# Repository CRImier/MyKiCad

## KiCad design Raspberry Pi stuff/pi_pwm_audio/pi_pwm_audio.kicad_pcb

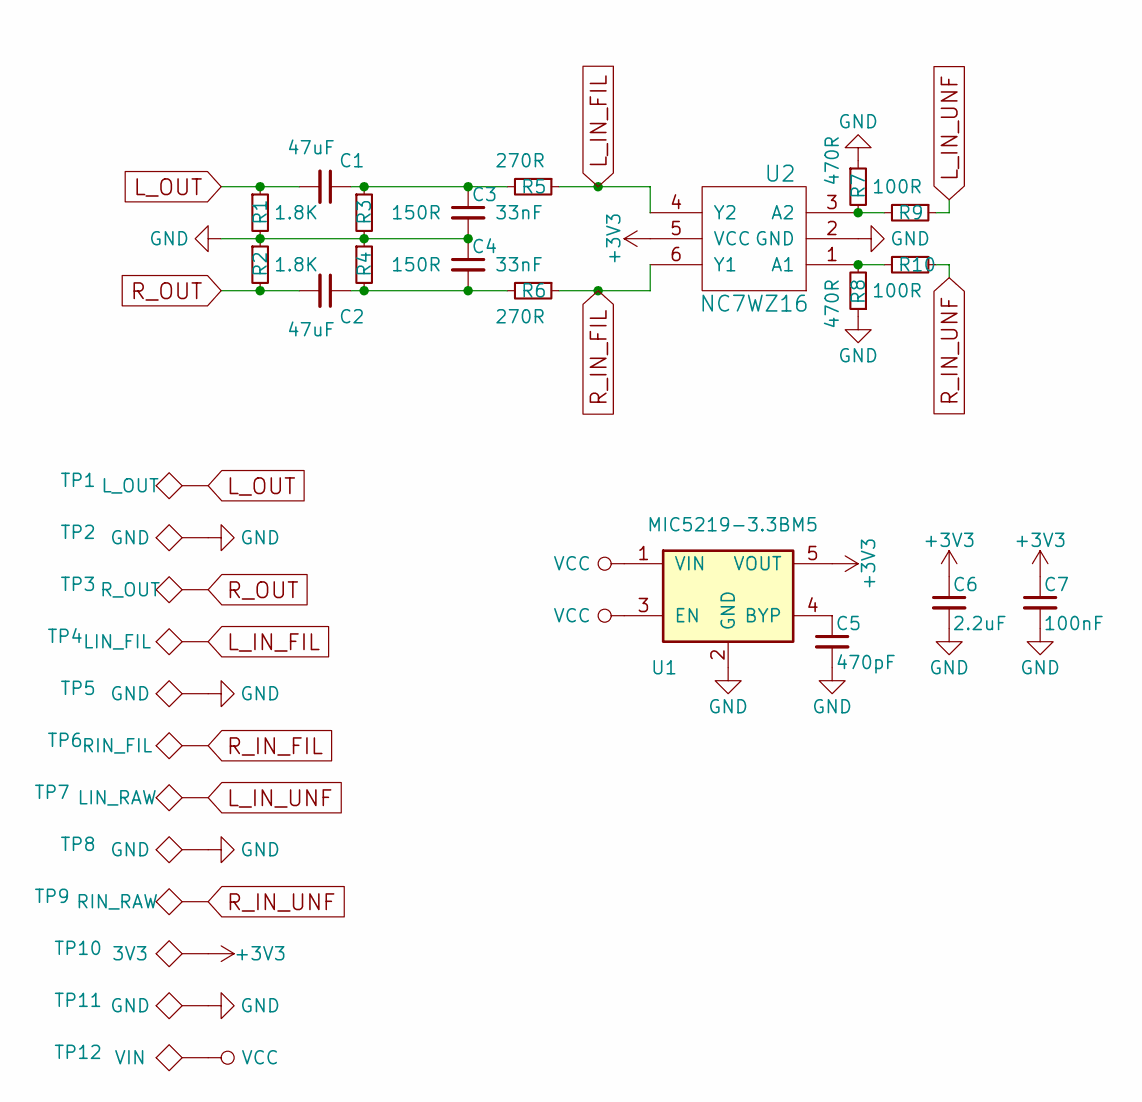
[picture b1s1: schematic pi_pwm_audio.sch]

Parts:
C1, C2: 47uF; C_1206_HandSoldering
C3, C4: 33nF; C_0603_HandSoldering
C5: 470pF; C_0603_HandSoldering
C6: 2.2uF; C_0805_HandSoldering
C7: 100nF; C_0805_HandSoldering
R1, R2: 1.8K; R_0603_HandSoldering
R3, R4: 150R; R_0603_HandSoldering
R5, R6: 270R; R_0603_HandSoldering
R7, R8: 470R; R_0603_HandSoldering
R9, R10: 100R; R_0603_HandSoldering
TP1: L_OUT; Measurement_Point_Round-TH_Small
TP2, TP5, TP8: GND; Measurement_Point_Square-TH_Small
TP3: R_OUT; Measurement_Point_Round-TH_Small
TP4: LIN_FIL; Measurement_Point_Round-TH_Small
TP6: RIN_FIL; Measurement_Point_Round-TH_Small
TP7: LIN_RAW; Measurement_Point_Round-TH_Small
TP9: RIN_RAW; Measurement_Point_Round-TH_Small
TP10: 3V3; Measurement_Point_Round-SMD-Pad_Small
TP11: GND; Measurement_Point_Round-SMD-Pad_Small
TP12: VIN; Measurement_Point_Round-TH_Small
U1: MIC5219-3.3BM5; SOT-23-5
U2: NC7WZ16; SOT-363_SC-70-6_Handsoldering

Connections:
+3V3: C6.1, C7.1, TP10.1, U1.5 (VOUT), U2.5 (VCC)
GND: C3.2, C4.1, C5.2, C6.2, C7.2, R1.2, R2.1, R3.2, R4.1, R7.1, R8.1, TP2.1, TP5.1, TP8.1, TP11.1, U1.2 (GND), U2.2 (GND)
L_IN_FIL: R5.1, TP4.1, U2.4 (Y2)
L_IN_UNF: R9.1, TP7.1
L_OUT: C1.2, R1.1, TP1.1
unnamed: C1.1, C3.1, R3.1, R5.2
unnamed: C2.1, C4.2, R4.2, R6.2
unnamed: C5.1, U1.4 (BYP)
unnamed: R7.2, R9.2, U2.3 (A2)
unnamed: R8.2, R10.2, U2.1 (A1)
R_IN_FIL: R6.1, TP6.1, U2.6 (Y1)
R_IN_UNF: R10.1, TP9.1
R_OUT: C2.2, R2.2, TP3.1
VCC: TP12.1, U1.1 (VIN), U1.3 (EN)

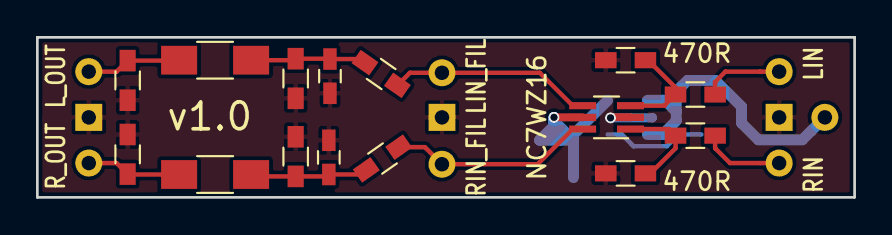
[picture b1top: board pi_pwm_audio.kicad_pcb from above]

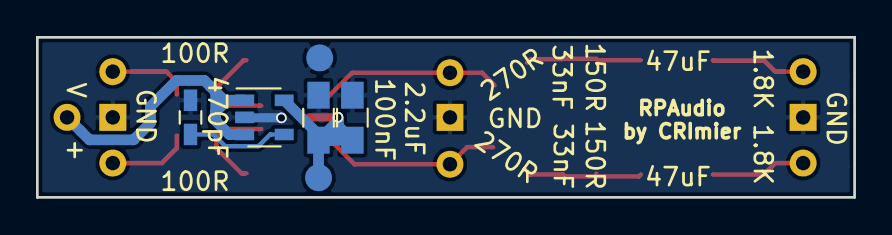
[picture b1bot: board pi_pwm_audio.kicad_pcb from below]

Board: 2 copper layers, 45.4 x 8.9 mm, 31 parts (6 on the bottom side), 14 nets.

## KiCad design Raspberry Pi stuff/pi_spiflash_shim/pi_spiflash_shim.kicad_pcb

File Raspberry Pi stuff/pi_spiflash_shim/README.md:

# Pi SPI flash shim

This board lets you reprogram SPI flash chips easily, by soldering the chip onto this board
and then plugging this board straight onto a Raspberry Pi GPIO header. Then, use something like flashrom.

The SPI chip is hardwired to CS0. The pin header holes are staggered in a way that should ensure
good mechanical contact of the plated holes to the Pi, without need for soldering.

Silkscreen markings on this board shows how many pin pairs you need to leave above and below,
decreasing the risk of you mis-plugging it.

This board is untested and there's no guarantees of fitness.

- Software: Kicad 6
- Version: 1
- PCB size: 19.05x12.7mm
- Layer count: 2
- Recommended thickness: whatever

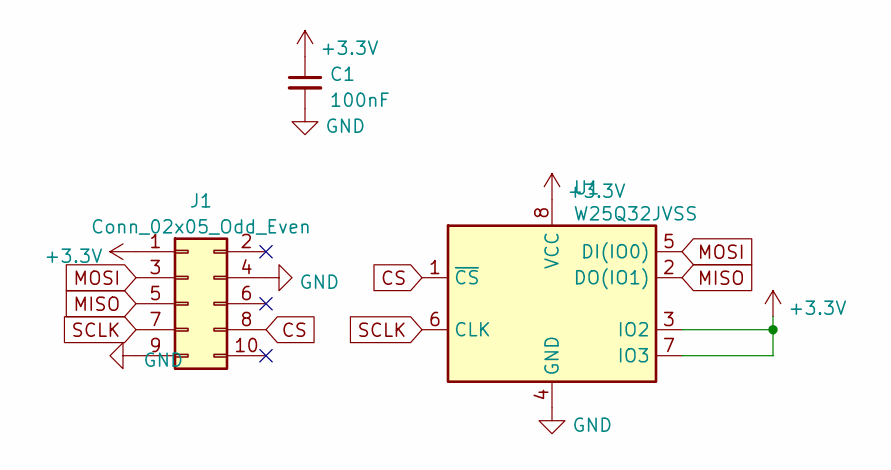
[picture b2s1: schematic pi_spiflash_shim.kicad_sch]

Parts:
C1: 100nF; C_0603_1608Metric
J1: Conn_02x05_Odd_Even; PinHeader_2x05_P2.54mm_Vertical
U1: W25Q32JVSS; SOIC-8_5.23x5.23mm_P1.27mm

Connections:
+3.3V: C1.1, J1.1, U1.3 (IO2), U1.7 (IO3), U1.8 (VCC)
CS: J1.8, U1.1 (~CS)
GND: C1.2, J1.4, J1.9, U1.4 (GND)
MISO: J1.5, U1.2 (DO(IO1))
MOSI: J1.3, U1.5 (DI(IO0))
SCLK: J1.7, U1.6 (CLK)

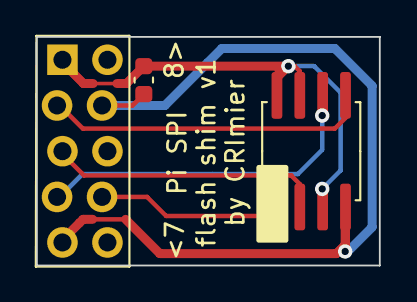
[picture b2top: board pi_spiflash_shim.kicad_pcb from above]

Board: 2 copper layers, 19.0 x 12.7 mm, 3 parts (0 on the bottom side), 6 nets.

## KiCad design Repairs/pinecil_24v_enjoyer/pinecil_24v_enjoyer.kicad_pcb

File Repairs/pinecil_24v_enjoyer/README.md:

# Pinecil 24V enjoyer

This is a board to add 24V support to a Pinecil. Main problem with 24V operation is VBUS of the Type-C FUSB302 IC,
and this board uses a resistor+zener combo to limit that to 20V (with the absolute maximum of the IC being 21V).
The VBUS trace to the IC has to be cut somehow and this board has to be soldered to the Pinecil PCB,
with "I" being soldered to the Pinecil's DC input, "O" soldered to the Type-C IC VBUS input
and "G" soldered to ground.

This board is currently untested and there's no guarantees of fitness.
It's also going to be hard to order anywhere due to its small size - I'll use mousebite panels and I suggest you do, too.

PCB markings on the bottom are "P24E v1", due to the board's small size.

Signal names are silkscreened on the board's bottom layers.

- PCB size: 7.5*5mm
- Layer count: 2
- Recommended thickness: 0.6mm/0.8mm (thin enough that it ought to fit inside the Pinecil; untested, though)

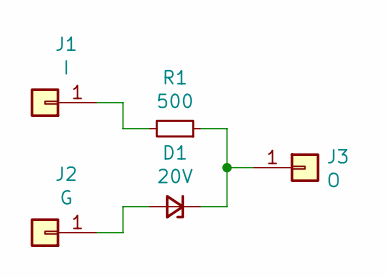
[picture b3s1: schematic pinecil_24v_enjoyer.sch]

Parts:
D1: 20V; D_SOD-123
J1: I; PinHeader_1x01_P2.00mm_Vertical
J2: G; PinHeader_1x01_P2.00mm_Vertical
J3: O; PinHeader_1x01_P2.00mm_Vertical
R1: 500; R_0805_2012Metric

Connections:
unnamed: D1.1 (K), J3.1, R1.1
unnamed: D1.2 (A), J2.1
unnamed: J1.1, R1.2

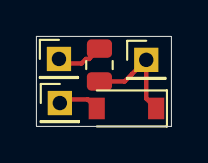
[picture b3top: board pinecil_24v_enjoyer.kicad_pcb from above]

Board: 2 copper layers, 7.5 x 5.0 mm, 5 parts (0 on the bottom side), 3 nets.

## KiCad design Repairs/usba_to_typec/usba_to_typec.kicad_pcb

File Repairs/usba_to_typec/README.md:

# USB-A to USB Type-C adapter

This is an adapter to backport USB-A 2.0 devices (i.e. flashdrives and pluggable devboards)
to USB Type-C. It has to be soldered in place of the USB-A connector, connecting all 4 pins
(GND, D+, D-, VBUS) to the pads on the board you're soldering to. Then, you'll be able
to use USB-C cables with your device!

Remove the 0R resistor if you don't need to pass VBUS to the device.

[Inspired by this project by Scott Alfter.](https://hackaday.io/project/161009-usb-micro-b-to-b-adapter-board):

- PCB size: 15.6*12.2mm
- Layer count: 2
- Recommended thickness: 1.6mm (so that the USB-C connector pins don't stick through the board)

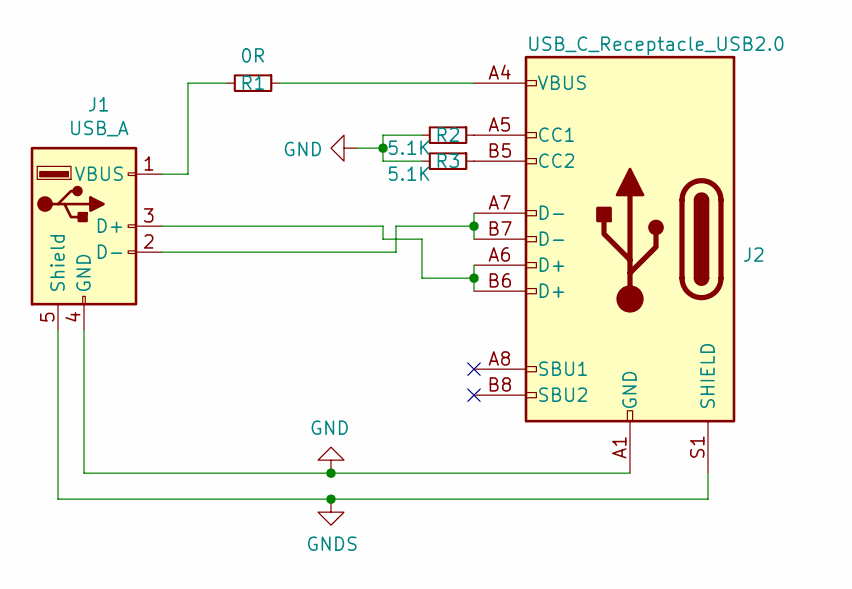
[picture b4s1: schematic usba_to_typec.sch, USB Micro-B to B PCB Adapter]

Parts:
J1: USB_A
J2: USB_C_Receptacle_USB2.0; USB_C_Receptacle_HRO_TYPE-C-31-M-12
R1: 0R; R_0805_2012Metric
R2, R3: 5.1K; R_0603_1608Metric

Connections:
GND: J1.4 (GND), J2.A1 (GND), J2.A12 (GND), J2.B1 (GND), J2.B12 (GND), R2.2, R3.2
GNDS: J1.5 (Shield), J2.S1 (SHIELD)
unnamed: J1.1 (VBUS), R1.2
unnamed: J1.2 (D-), J2.A7 (D-), J2.B7 (D-)
unnamed: J1.3 (D+), J2.A6 (D+), J2.B6 (D+)
unnamed: J2.A4 (VBUS), J2.A9 (VBUS), J2.B4 (VBUS), J2.B9 (VBUS), R1.1
unnamed: J2.A5 (CC1), R2.1
unnamed: J2.B5 (CC2), R3.1

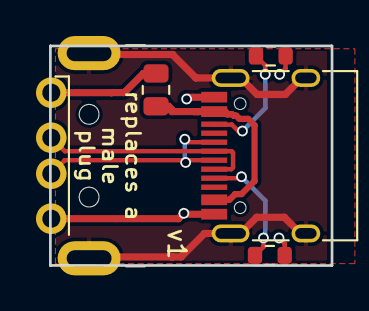
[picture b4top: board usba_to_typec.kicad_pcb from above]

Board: 2 copper layers, 15.6 x 12.2 mm, 5 parts (0 on the bottom side), 8 nets.

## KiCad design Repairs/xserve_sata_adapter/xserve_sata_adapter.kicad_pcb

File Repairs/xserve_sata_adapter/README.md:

# XServe SSD connector to M.2 B-key SSD adapter

This is a board that takes a (reverse-engineered) SATA SSD connector on the Apple Xserve board
and connects a B-key M.2 SSD slot to it. It's REed without having the adapter on hand, using
the pinout information available online and filling in the gaps where needed.

Power signal names are silkscreened on the board's bottom layer.
This board is untested and there's no guarantees of fitness.

- PCB size: 24x26mm
- Layer count: 2
- Recommended thickness: low (if the adapter is too thick, the server lid might not close).

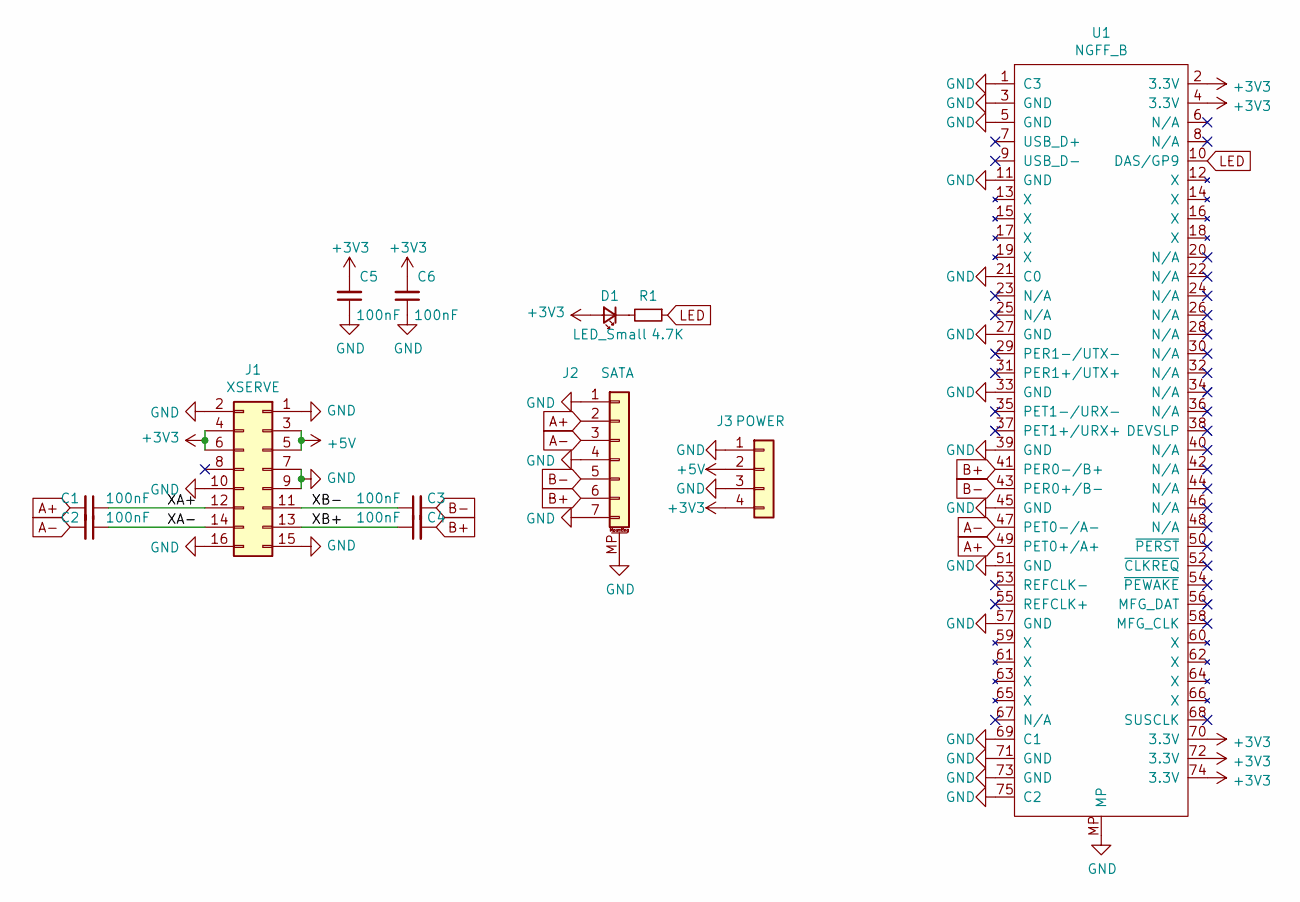
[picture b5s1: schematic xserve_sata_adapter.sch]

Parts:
C1, C2, C3, C4: 100nF; C_0402_1005Metric_Pad0.74x0.62mm_HandSolder
C5, C6: 100nF; C_0805_2012Metric
D1: LED_Small; LED_0805_2012Metric
J1: XSERVE; PinSocket_2x08_P1.27mm_Vertical_SMD
J2: SATA
J3: POWER; PinHeader_1x04_P2.54mm_Vertical
R1: 4.7K; R_0805_2012Metric
U1: NGFF_B; Conn_TE-M.2-0.5-67P-doublesided_TypeB

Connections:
+3V3: C5.2, C6.2, D1.2 (A), J1.4, J1.6, J3.4, U1.2 (3.3V), U1.4 (3.3V), U1.70 (3.3V), U1.72 (3.3V), U1.74 (3.3V)
+5V: J1.3, J1.5, J3.2
/XA+: C1.1, J1.12
/XA-: C2.1, J1.14
/XB+: C4.1, J1.13
/XB-: C3.1, J1.11
A+: C1.2, J2.2, U1.49 (PET0+/A+)
A-: C2.2, J2.3, U1.47 (PET0-/A-)
B+: C4.2, J2.6, U1.41 (PER0-/B+)
B-: C3.2, J2.5, U1.43 (PER0+/B-)
GND: C5.1, C6.1, J1.1, J1.2, J1.7, J1.9, J1.10, J1.15, J1.16, J2.1, J2.4, J2.7, J2.MP (MountPin), J3.1, J3.3, U1.1 (C3), U1.3 (GND), U1.5 (GND), U1.11 (GND), U1.21 (C0), U1.27 (GND), U1.33 (GND), U1.39 (GND), U1.45 (GND), U1.51 (GND), U1.57 (GND), U1.69 (C1), U1.71 (GND), U1.73 (GND), U1.75 (C2), U1.MP
LED: R1.1, U1.10 (DAS/GP9)
unnamed: D1.1 (K), R1.2

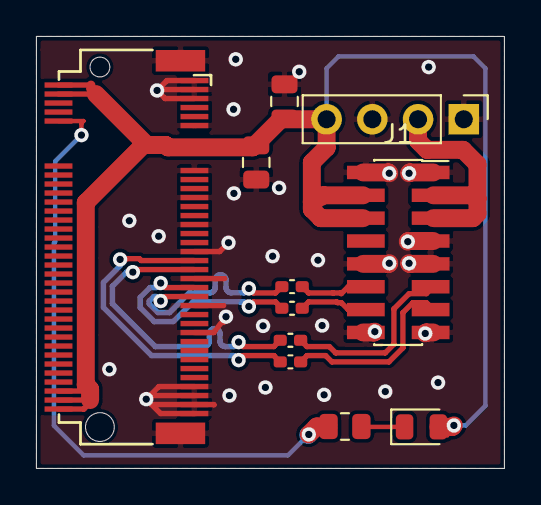
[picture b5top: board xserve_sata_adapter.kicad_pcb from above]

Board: 2 copper layers, 26.0 x 24.0 mm, 11 parts (0 on the bottom side), 13 nets.

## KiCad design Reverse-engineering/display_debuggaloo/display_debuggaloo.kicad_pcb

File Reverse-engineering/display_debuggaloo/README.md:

# Display Debuggaloo

This is an "interposer" board for reverse-engineering LCD and other displays with a logic analyzer.
that communicate using SPI or I2C, every signal gets 3 pins. One pin is meant for "input",
other is meant for "output" (to the display) and the third is meant for the logic analyzer.
This board also has 6.8 screw holes in case you want to mount it somewhere in a more permanent way.
It also has two separate testpoints for VCC, I no longer remember why I added those.

## Notes

- Signal names are printed using soldermask, on top and bottom layers.
- This board is untested and there's no guarantees of fitness.

## Info

- Software: Kicad 7
- Version: 1
- PCB size: 24.15*30.48mm
- Layer count: 2

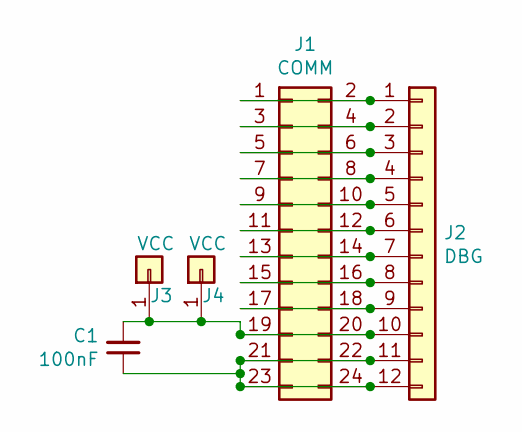
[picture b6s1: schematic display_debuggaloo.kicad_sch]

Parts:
C1: 100nF; C_0805_2012Metric
J1: COMM; PinHeader_2x12_P2.54mm_Vertical
J2: DBG; PinHeader_1x12_P2.54mm_Vertical
J3, J4: VCC; PinHeader_1x01_P2.54mm_Vertical

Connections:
unnamed: C1.1, J1.21, J1.22, J1.23, J1.24, J2.11, J2.12
unnamed: C1.2, J1.19, J1.20, J2.10, J3.1, J4.1
unnamed: J1.1, J1.2, J2.1
unnamed: J1.3, J1.4, J2.2
unnamed: J1.5, J1.6, J2.3
unnamed: J1.7, J1.8, J2.4
unnamed: J1.9, J1.10, J2.5
unnamed: J1.11, J1.12, J2.6
unnamed: J1.13, J1.14, J2.7
unnamed: J1.15, J1.16, J2.8
unnamed: J1.17, J1.18, J2.9

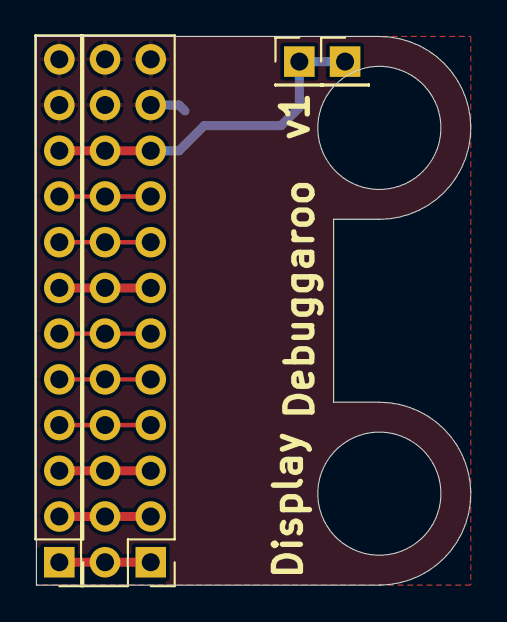
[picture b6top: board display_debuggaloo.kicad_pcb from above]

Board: 2 copper layers, 24.1 x 30.5 mm, 5 parts (1 on the bottom side), 11 nets.

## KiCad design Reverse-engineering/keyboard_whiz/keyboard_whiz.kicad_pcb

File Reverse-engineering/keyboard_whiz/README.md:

# KeyboardWhiz

A keyboard matrix reverse-engineering tool - to help reverse-engineer laptop and
other keyboards. Uses two MCP23017 expanders connected to the same I2C bus, requires
a host with I2C port (i.e. a Raspberry Pi) to scan the keyboard rows&columns,
detect keypresses and help user map the row&column combinations to keys.
It can also be used as a GPIO expander over I2C.

V1 has an 1mm, 0.8mm and 0.5mm connector for the keyboard, as well as an RPi
HAT connector and a 5-pin I2C connector (for connecting the board to i.e.
a ZeroPhone). V2 has the same, but keeys everything within the Pi HAT outline.

V3, in addition to these, has a RP2040 with a USB-C connector that controls everything,
allowing control from the Pi or an I2C header still. This lets the KeyboardWhiz work as an
independent controller for laptop keyboards.

- This repository also includes files for manufacturing a 1x2 panel.
- This board is untested and there's no guarantees of fitness.
- I recommend a stencil for assembling this board.

- Software: Kicad 6
- Version: 3
- PCB size: 65x56mm
- Layer count: 2
- Recommended thickness: non-thin

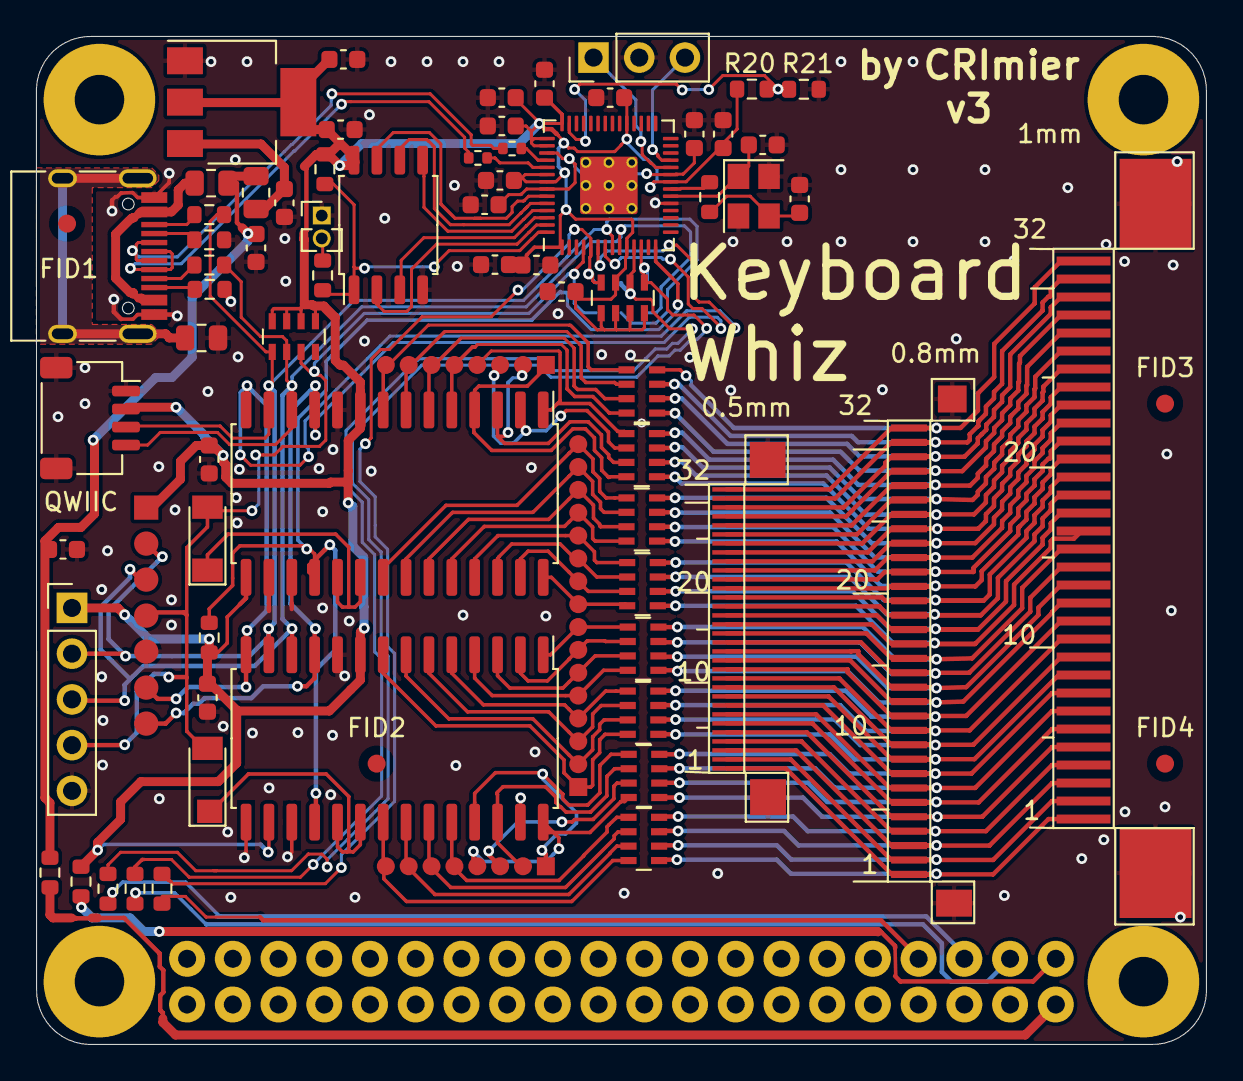
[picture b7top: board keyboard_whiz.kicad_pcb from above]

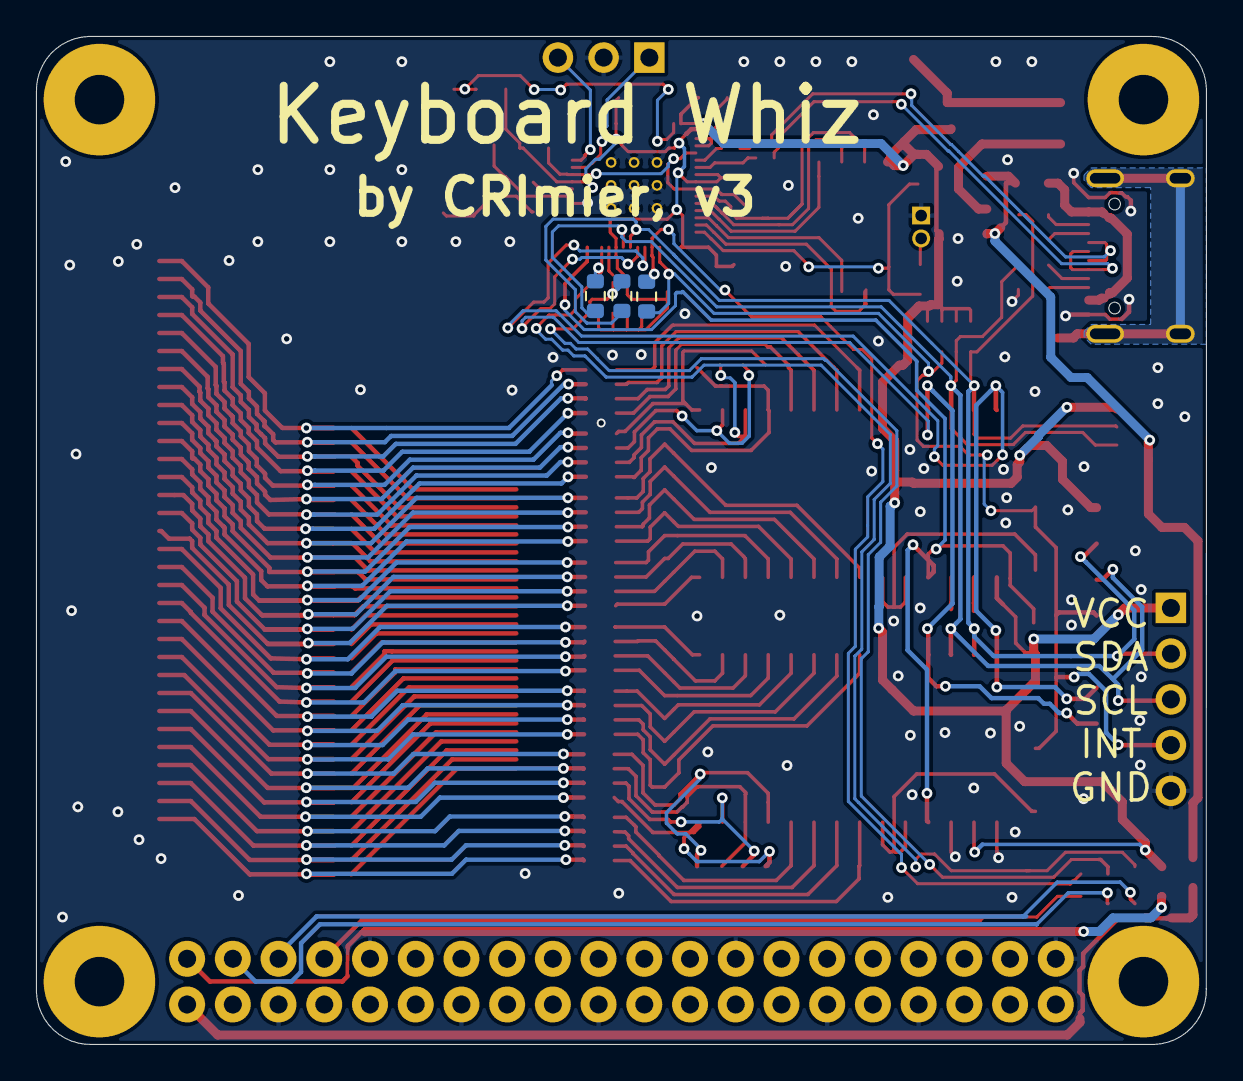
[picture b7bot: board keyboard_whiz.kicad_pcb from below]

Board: 2 copper layers, 65.0 x 56.0 mm, 78 parts (3 on the bottom side), 108 nets.

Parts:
C1, C2, C5, C6, C7, C8, C9, C10, C11, C12, C13, C14, C15, C16, C17, C18, C19, C20: 100nF; C_0603_1608Metric
C3, C4: Cc; C_0603_1608Metric
D1, D2: 1N4148; D_MiniMELF
FID1, FID2, FID3, FID4: Fiducial; Fiducial_1mm_Mask2mm
J1: I2C; PinHeader_1x05_P2.54mm_Vertical
J2: 0.5mm; FPC_40_0.5mm
J3: 0.8mm; FPC_40_0.8mm
J4: 1mm; FPC_40_1mm
J5: Raspberry_Pi_2_3; RASPBERRY_PI_HAT
J6: IO_o1; PinHeader_1x08_P1.27mm_Vertical
J7: IO_o2; PinHeader_1x16_P1.27mm_Vertical
J8: IO_o3; PinHeader_1x08_P1.27mm_Vertical
J9: USB_C_Receptacle_USB2.0; USB_C_Receptacle_HRO_TYPE-C-31-M-12
J10: SWD; PinHeader_1x03_P2.54mm_Vertical
J11: BOOT; PinHeader_1x02_P1.27mm_Vertical
J12: QWIIC; JST_SH_SM04B-SRSS-TB_1x04-1MP_P1.00mm_Horizontal
J13: IO_DT; PinHeader_1x07_P2.00mm_Vertical
R1, R3, R4: 5K1; R_0603_1608Metric
R2, R19, R23: 0/F; R_0805_2012Metric
R5, R6: 22R; R_0402_1005Metric
R7, R8: 1K; R_0603_1608Metric
R9: 10K; R_0603_1608Metric
R10, R11, R12, R13, R14, R15, R16, R17, R18, R22: 0R; R_0603_1608Metric
R20: A; R_0603_1608Metric
R21: B; R_0603_1608Metric
RN1, RN2: 10K; R_Array_Concave_4x0603
RN9, RN10, RN11, RN12, RN13, RN14, RN15, RN16: R_Pack04; R_Array_Concave_4x0603
U1: 0x21; SOIC-28W_7.5x17.9mm_P1.27mm
U2: 0x22; SOIC-28W_7.5x17.9mm_P1.27mm
U3: W25Q32JVSS; SOIC-8_5.23x5.23mm_P1.27mm
U4: RP2040; RP2040-QFN-56
U5: AP1117-33; SOT-223-3_TabPin2
Y1: 12MHz; Crystal_SMD_3225-4Pin_3.2x2.5mm

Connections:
+1V1: C12.1, C16.1, U4.23, U4.45, U4.50
+3V3: C1.1, C2.1, C5.1, C6.1, C7.1, C8.1, C9.1, C10.1, C11.1, C13.1, C14.1, C15.1, C20.1, J1.1, J12.2, J13.1, R1.2, R9.1, R12.1, R20.1, RN1.3, RN1.5, RN1.6, RN1.7, RN1.8, RN2.5, RN2.6, RN2.7, RN2.8, U1.9, U1.15, U2.9, U2.16, U3.8, U4.1, U4.10, U4.22, U4.33, U4.42, U4.43, U4.44, U4.48, U4.49, U5.2
+5V: C17.1, C18.1, R2.1, R19.2, R22.1
+5VD: J5.2, R22.2
+5VL: C19.1, R19.1, U5.3
/C0: J2.1, J3.1, J4.1, RN15.1
/C1: J2.2, J3.2, J4.2, RN15.2
/C2: J2.3, J3.3, J4.3, RN15.3
/C3: J2.4, J3.4, J4.4, RN15.4
/C4: J2.5, J3.5, J4.5, RN16.1
/C5: J2.6, J3.6, J4.6, RN16.2
/C6: J2.7, J3.7, J4.7, RN16.3
/C7: J2.8, J3.8, J4.8, RN16.4
/C8: J2.9, J3.9, J4.9, RN13.1
/C9: J2.10, J3.10, J4.10, RN13.2
/C10: J2.11, J3.11, J4.11, RN13.3
/C11: J2.12, J3.12, J4.12, RN13.4
/C12: J2.13, J3.13, J4.13, RN14.1
/C13: J2.14, J3.14, J4.14, RN14.2
/C14: J2.15, J3.15, J4.15, RN14.3
/C15: J2.16, J3.16, J4.16, RN14.4
/C16: J2.17, J3.17, J4.17, RN11.1
/C17: J2.18, J3.18, J4.18, RN11.2
/C18: J2.19, J3.19, J4.19, RN11.3
/C19: J2.20, J3.20, J4.20, RN11.4
/C20: J2.21, J3.21, J4.21, RN12.1
/C21: J2.22, J3.22, J4.22, RN12.2
/C22: J2.23, J3.23, J4.23, RN12.3
/C23: J2.24, J3.24, J4.24, RN12.4
/C24: J2.25, J3.25, J4.25, RN9.1
/C25: J2.26, J3.26, J4.26, RN9.2
/C26: J2.27, J3.27, J4.27, RN9.3
/C27: J2.28, J3.28, J4.28, RN9.4
/C28: J2.29, J3.29, J4.29, RN10.1
/C29: J2.30, J3.30, J4.30, RN10.2
/C30: J2.31, J3.31, J4.31, RN10.3
/C31: J2.32, J3.32, J4.32, RN10.4
/O0: J6.8, RN15.8, U2.21
/O1: J6.7, RN15.7, U2.22
/O2: J6.6, RN15.6, U2.23
/O3: J6.5, RN15.5, U2.24
/O4: J6.4, RN16.8, U2.28
/O5: J6.3, RN16.7, U2.27
/O6: J6.2, RN16.6, U2.26
/O7: J6.1, RN16.5, U2.25
/O8: J7.1, RN13.8, U2.8
/O9: J7.2, RN13.7, U2.7
/O10: J7.3, RN13.6, U2.6
/O11: J7.4, RN13.5, U2.5
/O12: J7.5, RN14.8, U2.4
/O13: J7.6, RN14.7, U2.3
/O14: J7.7, RN14.6, U2.2
/O15: J7.8, RN14.5, U2.1
/O16: J7.9, RN11.8, U1.28
/O17: J7.10, RN11.7, U1.27
/O18: J7.11, RN11.6, U1.26
/O19: J7.12, RN11.5, U1.25
/O20: J7.13, RN12.8, U1.24
/O21: J7.14, RN12.7, U1.23
/O22: J7.15, RN12.6, U1.22
/O23: J7.16, RN12.5, U1.21
/O24: J8.1, RN9.8, U1.4
/O25: J8.2, RN9.7, U1.3
/O26: J8.3, RN9.6, U1.2
/O27: J8.4, RN9.5, U1.1
/O28: J8.5, RN10.8, U1.5
/O29: J8.6, RN10.7, U1.6
/O30: J8.7, RN10.6, U1.7
/O31: J8.8, RN10.5, U1.8
/SHD: J9.S1, R23.2
CS: J13.7, U1.11, U2.11, U4.7
D+: J9.A6, J9.B6, R6.2
D-: J9.A7, J9.B7, R5.2
GND: C1.2, C2.2, C3.1, C4.2, C5.2, C6.2, C7.2, C8.2, C9.2, C10.2, C11.2, C12.2, C13.2, C14.2, C15.2, C16.2, C17.2, C18.2, C19.2, C20.2, J1.5, J2.MP, J3.MP, J4.MP, J5.6, J5.9, J5.14, J5.20, J5.25, J5.30, J5.34, J5.39, J9.A1, J9.A12, J9.B1, J9.B12, J10.2, J11.1, J12.1, J12.MP, J13.5, R3.2, R4.2, R21.2, R23.1, U1.10, U1.16, U1.17, U2.10, U2.15, U2.17, U3.4, U4.19, U4.57, U5.1, Y1.2, Y1.4
ID: R20.2, R21.1, U4.41
INT: D1.2, D2.2, J1.4, J13.4, R15.1, RN2.3, U4.4
INTO1: D1.1, U1.19, U1.20
INTO2: D2.1, U2.19, U2.20
IRST: R1.1, U1.18, U2.18, U4.14
unnamed: C3.2, U4.20, Y1.1
unnamed: C4.1, R7.1, Y1.3
unnamed: J9.A4, J9.A9, J9.B4, J9.B9, R2.2
unnamed: J9.A5, R3.1
unnamed: J9.A8, R10.1
unnamed: J9.B5, R4.1
unnamed: J9.B8, R11.1
unnamed: J10.1, U4.24
unnamed: J10.3, U4.25
unnamed: J11.2, R8.2
unnamed: R7.2, U4.21
PINT: R15.2, R18.1, RN1.4, U4.5
PSCL: R14.2, R17.1, RN1.1, U4.12
PSDA: R13.2, R16.1, RN1.2, U4.11
QCK: U3.6, U4.52
QD0: U3.5, U4.53
QD1: U3.2, U4.55
QD2: U3.3, U4.54
QD3: U3.7, U4.51
QSS: R8.1, R9.2, U3.1, U4.56
RD+: R6.1, U4.47
RD-: R5.1, U4.46
RINT: J5.7, R18.2
RSCL: J5.5, R17.2
RSDA: J5.3, R16.2
SCL: J1.3, J12.4, J13.3, R10.2, R14.1, RN2.2, U1.12, U2.12, U4.9
SDA: J1.2, J12.3, J13.2, R11.2, R13.1, RN2.1, U1.13, U2.13, U4.8
SO: J13.6, U1.14, U2.14, U4.6
VCC: J5.1, R12.2
